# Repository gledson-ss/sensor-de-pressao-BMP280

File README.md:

# 📚 Objetivos / finalidade
Criar um dispositivo capaz de realizar medições contínuas de temperatura, pressão e altitude com a finalidade de fornecer ao usuário tais dados, para que o mesmo possa realizar inferências. As informações serão fornecidas pelo sensor _BMP280_, que há de comunicar-se com o _RP2040_ através do protocolo _I2C_. Além disso, o microcontrolador também processará e fornecerá as informações necessárias para display _LCD_, que por sua vez, realiza a exibição das informações periodicamente para o usuário. 

# Motivos da escolha dos componentes utilizados para resolver o problema:
- _RP2040_: A escolha do microcontrolador deu-se como sugestão do professor.
- _BMP280_: foi escolhido em contraproposta ao _BMP270_ pois o primeiro é menor e mais veloz, portanto mais eficiente.
- _LCD 16x2_: Para realizar uma exibição amigável dos dados de interesse para o usuário. 
- _PCF8574_: Nosso display _LCD_ não comunica-se utilizando _I2C_, então para normalizar a comunicação buscamos um CI para tal função.

# Problemas e dificuldades encontrados:
1. Testar o código: Como não possuímos o hardware em mãos, não tivemos como realizar testes concretos. Boa parte do nosso desenvolvimento baseou-se em exemplos de implementação de casos similares encontrados na internet. 
2. Encontrar circuito para realizar a comunicação _I2C_ entre o microcontrolador e o display
3. Realizar o roteamento da placa

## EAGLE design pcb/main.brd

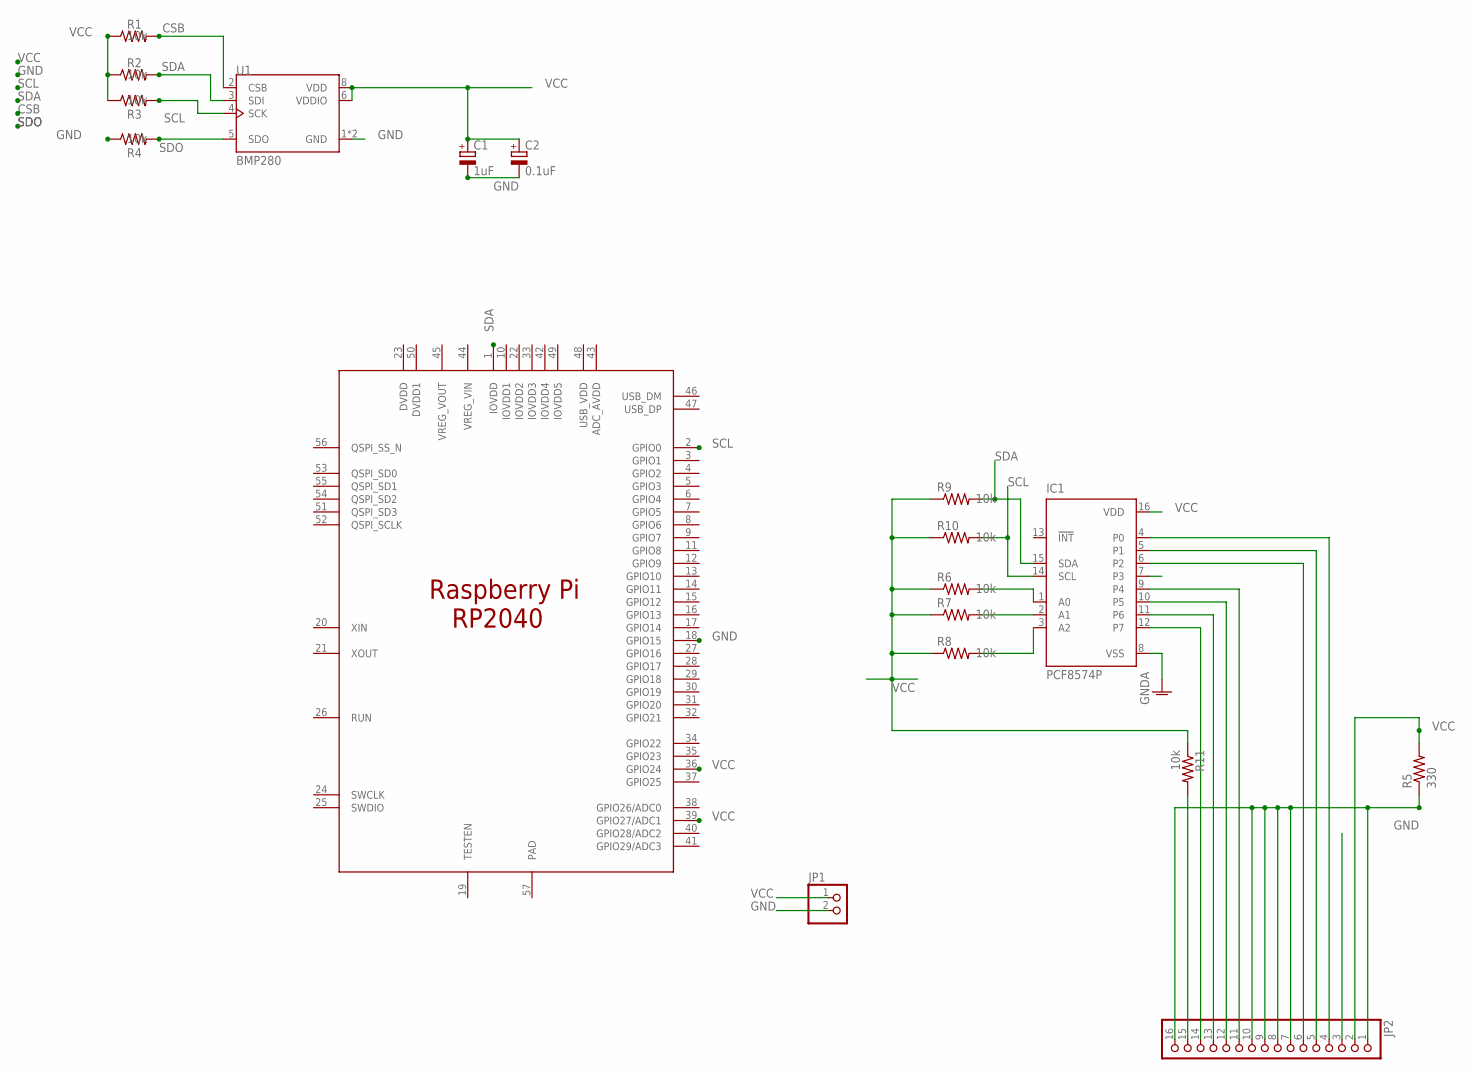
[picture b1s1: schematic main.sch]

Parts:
C1: 1uF; E2-5
C2: 0.1uF; E2-5
IC1: PCF8574P; DIL16
JP1: PINHD-1X2; 1X02
JP2: PINHD-1X16; 1X16
R1, R2, R3, R4, R6, R7, R8, R9, R10, R11: 10k; 0204/7
R5: 330; 0204/7
U1: BMP280; XDCR_BMP280
U$1: RP2040; QFN40P695X695X90-57T320N

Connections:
CSB: R1.2, U1.2 (CSB)
GND: C1.-, C2.-, JP1.2, JP2.1, JP2.7, JP2.8, JP2.9, JP2.10, JP2.16, R4.1, R5.1, U1.1 (GND), U1.7 (GND), U$1.18 (GPIO15)
GNDA: IC1.8 (VSS)
unnamed: IC1.12 (P7), JP2.14
unnamed: IC1.11 (P6), JP2.13
unnamed: IC1.10 (P5), JP2.12
unnamed: IC1.9 (P4), JP2.11
unnamed: IC1.4 (P0), JP2.4
unnamed: IC1.5 (P1), JP2.5
unnamed: IC1.6 (P2), JP2.6
unnamed: IC1.1 (A0), R6.2
unnamed: IC1.2 (A1), R7.2
unnamed: IC1.3 (A2), R8.2
unnamed: JP2.15, R11.2
SCL: IC1.14 (SCL), R3.2, R10.2, U1.4 (SCK), U$1.2 (GPIO0)
SDA: IC1.15 (SDA), R2.2, R9.2, U1.3 (SDI), U$1.1 (IOVDD)
SDO: R4.2, U1.5 (SDO)
VCC: C1.+, C2.+, IC1.16 (VDD), JP1.1, JP2.2, R1.1, R2.1, R3.1, R5.2, R6.1, R7.1, R8.1, R9.1, R10.1, R11.1, U1.6 (VDDIO), U1.8 (VDD), U$1.36 (GPIO24), U$1.39 (GPIO27/ADC1)

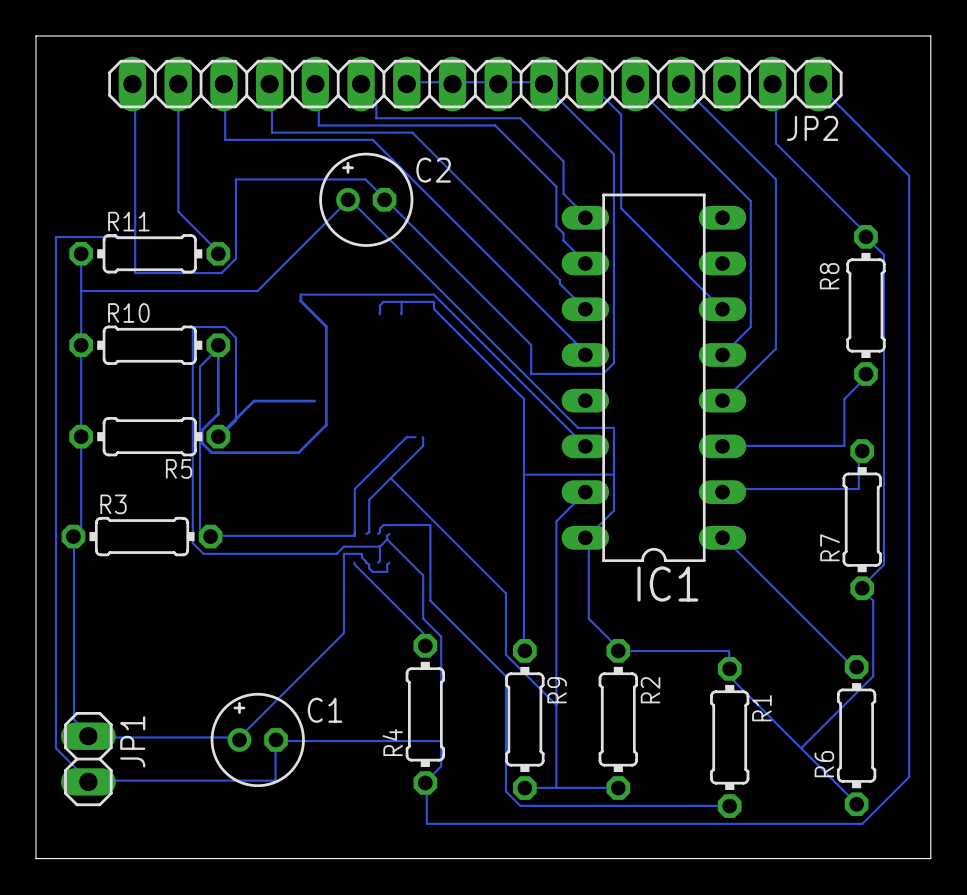
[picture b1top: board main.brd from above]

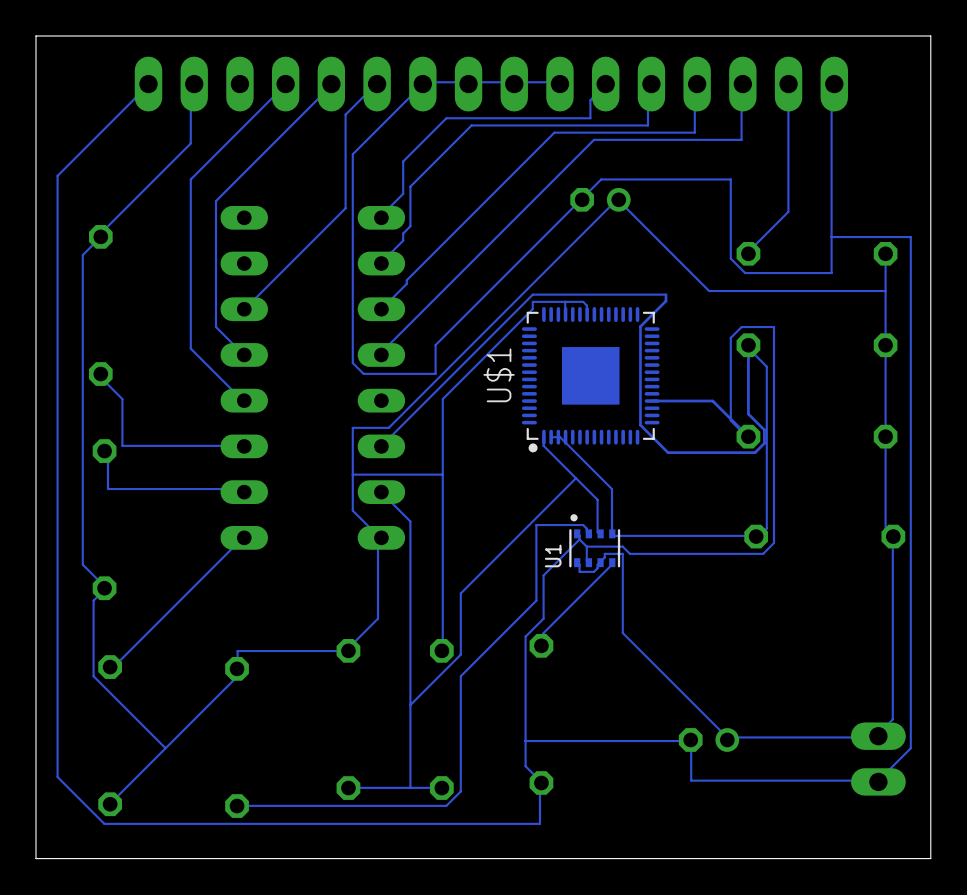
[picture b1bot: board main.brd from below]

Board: 2 copper layers, 49.7 x 45.7 mm, 18 parts (2 on the bottom side), 17 nets.

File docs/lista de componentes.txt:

Partlist exported from C:/Users/Erick/Documents/EAGLE/projects/Proejto BMP280/main.sch at 21/09/2021 19:18

Part Value         Device        Package                  Description                                                                                   
C1   1uF           CPOL-EUE2-5   E2-5                     POLARIZED CAPACITOR, European symbol                                                          
C2   0.1uF         CPOL-EUE2-5   E2-5                     POLARIZED CAPACITOR, European symbol                                                          
DIS1 TUXGR_16X2_R2 TUXGR_16X2_R2 TUXGR_16X2_R2            Tuxgraphics LCD display 16x2 characters reflective, without background light                  
IC1  PCF8574P      PCF8574P      DIL16                    I2C-Bus Remote 8-bit I/O expander                                                             
JP1                PINHD-1X2     1X02                     PIN HEADER                                                                                    
JP2                PINHD-1X16    1X16                     PIN HEADER                                                                                    
R1   10k           R-US_0204/7   0204/7                   RESISTOR, American symbol                                                                     
R2   10k           R-US_0204/7   0204/7                   RESISTOR, American symbol                                                                     
R3   10k           R-US_0204/7   0204/7                   RESISTOR, American symbol                                                                     
R4   10k           R-US_0204/7   0204/7                   RESISTOR, American symbol                                                                     
R5   330           R-US_0204/7   0204/7                   RESISTOR, American symbol                                                                     
R6   10k           R-US_0204/7   0204/7                   RESISTOR, American symbol                                                                     
R7   10k           R-US_0204/7   0204/7                   RESISTOR, American symbol                                                                     
R8   10k           R-US_0204/7   0204/7                   RESISTOR, American symbol                                                                     
R9   10k           R-US_0204/7   0204/7                   RESISTOR, American symbol                                                                     
R10  10k           R-US_0204/7   0204/7                   RESISTOR, American symbol                                                                     
R11  10k           R-US_0204/7   0204/7                   RESISTOR, American symbol                                                                     
U$1  RP2040        RP2040        QFN40P695X695X90-57T320N Check prices                                                                                  
U1   BMP280        BMP280        XDCR_BMP280              BMP280

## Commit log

2021-07-05 started repo
2021-08-05 changed folder
2021-08-07 datasheet BMP280 adicionado
2021-08-07 datasheet RP2040 adicionado
2021-08-07 Descricao projeto adicionada
2021-09-21 add files
2021-09-21 deleted file
2021-10-05 Move files of place and change behavior
2021-10-08 code refactoring
2021-10-14 Update main file
2021-10-14 Update pcb files
2021-10-14 Update videos
2021-10-19 Add case
2021-10-19 Add other files
